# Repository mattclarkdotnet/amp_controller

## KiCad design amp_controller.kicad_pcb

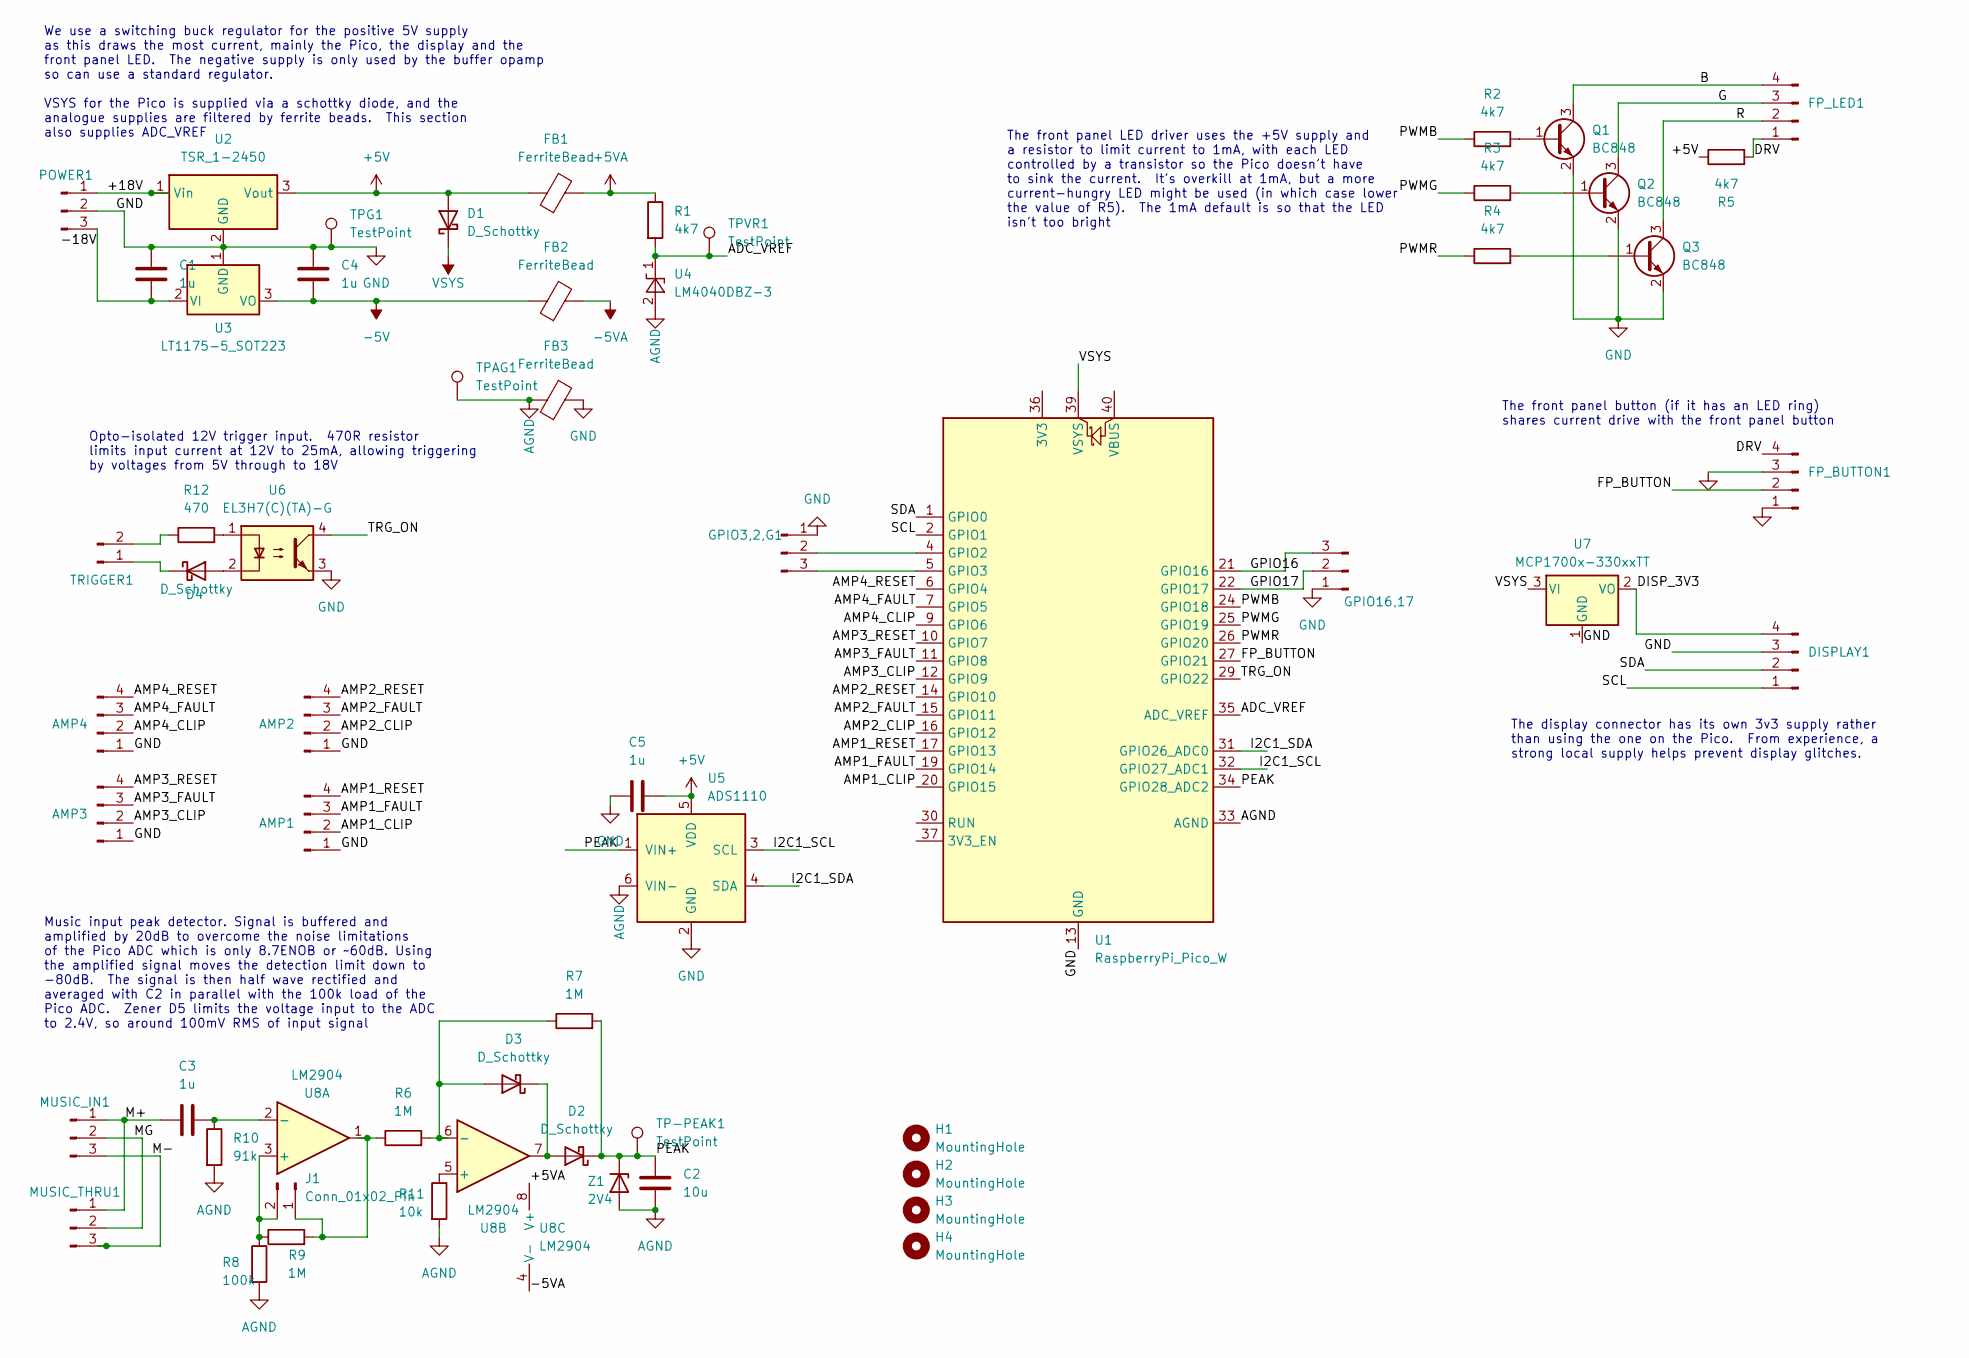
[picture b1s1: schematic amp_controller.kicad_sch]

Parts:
AMP1, AMP2, AMP3, AMP4: Conn_01x04_Pin; JST_EH_B4B-EH-A_1x04_P2.50mm_Vertical
C1, C3, C4, C5: 1u; C_0805_2012Metric; LCSC C28323
C2: 10u; C_0805_2012Metric; LCSC C440198
D1, D2, D3, D4: D_Schottky; D_SOD-523; LCSC C145179
DISPLAY1: Conn_01x04_Pin; JST_EH_B4B-EH-A_1x04_P2.50mm_Vertical
FB1, FB2, FB3: FerriteBead; L_0805_2012Metric; LCSC C1015
FP_BUTTON1: Conn_01x04_Pin; JST_EH_B4B-EH-A_1x04_P2.50mm_Vertical
FP_LED1: Conn_01x04_Pin; JST_EH_B4B-EH-A_1x04_P2.50mm_Vertical
GPIO3,2,G1, GPIO16,17: Conn_01x02_Pin; PinHeader_1x03_P2.54mm_Vertical
H1, H2, H3, H4: MountingHole; MountingHole_3.2mm_M3
J1: Conn_01x02_Pin; PinHeader_1x02_P2.54mm_Vertical
MUSIC_IN1: Conn_01x03_Pin; JST_EH_B3B-EH-A_1x03_P2.50mm_Vertical
MUSIC_THRU1: Conn_01x03_Pin; JST_EH_B3B-EH-A_1x03_P2.50mm_Vertical
POWER1: Conn_01x03_Pin; TerminalBlock_Phoenix_PT-1,5-3-3.5-H_1x03_P3.50mm_Horizontal
Q1, Q2, Q3: BC848; SOT-723; LCSC C2923360
R1, R2, R3, R4, R5: 4k7; R_0805_2012Metric; LCSC C17673
R6, R7, R9: 1M; R_0805_2012Metric; LCSC C17514
R8: 100k; R_0805_2012Metric; LCSC C149504
R10: 91k; R_0805_2012Metric; LCSC C2930321
R11: 10k; R_0805_2012Metric; LCSC C17414
R12: 470; R_0805_2012Metric; LCSC C17710
TP-PEAK1: TestPoint; TestPoint_THTPad_1.0x1.0mm_Drill0.5mm
TPAG1: TestPoint; TestPoint_THTPad_1.0x1.0mm_Drill0.5mm
TPG1: TestPoint; TestPoint_THTPad_1.0x1.0mm_Drill0.5mm
TPVR1: TestPoint; TestPoint_THTPad_1.0x1.0mm_Drill0.5mm
TRIGGER1: Conn_01x02_Pin; JST_EH_B2B-EH-A_1x02_P2.50mm_Vertical
U1: RaspberryPi_Pico_W; RaspberryPi_Pico_W_SMD
U2: TSR_1-2450; Converter_DCDC_TRACO_TSR-1_THT
U3: LT1175-5_SOT223; SOT-89-3; LCSC C122849
U4: LM4040DBZ-3; SOT-23; LCSC C181416
U5: ADS1110; SOT-23-6; LCSC C16598
U6: EL3H7(C)(TA)-G; SOIC-4_4.55x2.6mm_P1.27mm; LCSC C92243
U7: MCP1700x-330xxTT; SOT-23; LCSC C5446
U8: LM2904; SO-8_3.9x4.9mm_P1.27mm; LCSC C2941725
Z1: 2V4; D_SOD-323; LCSC C268469

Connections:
+5V: C5.2, D1.2 (A), FB1.1, R5.1, U2.3 (Vout), U5.5 (VDD)
+5VA: FB1.2, R1.1, U8.8 (V+)
-5V: C4.2, FB2.1, U3.3 (VO)
-5VA: FB2.2, U8.4 (V-)
/+18V: POWER1.1, U2.1 (Vin)
/-18V: C1.2, POWER1.3, U3.2 (VI)
/ADC_VREF: R1.2, TPVR1.1, U1.35 (ADC_VREF), U4.1 (K)
/AMP1_CLIP: AMP1.2, U1.20 (GPIO15)
/AMP1_FAULT: AMP1.3, U1.19 (GPIO14)
/AMP1_RESET: AMP1.4, U1.17 (GPIO13)
/AMP2_CLIP: AMP2.2, U1.16 (GPIO12)
/AMP2_FAULT: AMP2.3, U1.15 (GPIO11)
/AMP2_RESET: AMP2.4, U1.14 (GPIO10)
/AMP3_CLIP: AMP3.2, U1.12 (GPIO9)
/AMP3_FAULT: AMP3.3, U1.11 (GPIO8)
/AMP3_RESET: AMP3.4, U1.10 (GPIO7)
/AMP4_CLIP: AMP4.2, U1.9 (GPIO6)
/AMP4_FAULT: AMP4.3, U1.7 (GPIO5)
/AMP4_RESET: AMP4.4, U1.6 (GPIO4)
/B: FP_LED1.4, Q1.3 (C)
/DISP_3V3: DISPLAY1.4, U7.2 (VO)
/DRV: FP_BUTTON1.4, FP_LED1.1, R5.2
/FP_BUTTON: FP_BUTTON1.2, U1.27 (GPIO21)
/G: FP_LED1.3, Q2.3 (C)
/GPIO16: GPIO16,17.3, U1.21 (GPIO16)
/GPIO17: GPIO16,17.2, U1.22 (GPIO17)
/I2C1_SCL: U1.32 (GPIO27_ADC1), U5.3 (SCL)
/I2C1_SDA: U1.31 (GPIO26_ADC0), U5.4 (SDA)
/M+: C3.1, MUSIC_IN1.1, MUSIC_THRU1.1
/M-: MUSIC_IN1.3, MUSIC_THRU1.3
/MG: MUSIC_IN1.2, MUSIC_THRU1.2
/PEAK: C2.1, D2.1 (K), R7.2, TP-PEAK1.1, U1.34 (GPIO28_ADC2), U5.1 (VIN+), Z1.1 (K)
/PWMB: R2.1, U1.24 (GPIO18)
/PWMG: R3.1, U1.25 (GPIO19)
/PWMR: R4.1, U1.26 (GPIO20)
/R: FP_LED1.2, Q3.3 (C)
/SCL: DISPLAY1.1, U1.2 (GPIO1)
/SDA: DISPLAY1.2, U1.1 (GPIO0)
/TRG_ON: U1.29 (GPIO22), U6.4
AGND: C2.2, FB3.1, R8.2, R10.2, R11.2, TPAG1.1, U1.33 (AGND), U4.2 (A), U5.6 (VIN-), Z1.2 (A)
GND: AMP1.1, AMP2.1, AMP3.1, AMP4.1, C1.1, C4.1, C5.1, DISPLAY1.3, FB3.2, FP_BUTTON1.1, FP_BUTTON1.3, GPIO3,2,G1.1, GPIO16,17.1, POWER1.2, Q1.2 (E), Q2.2 (E), Q3.2 (E), TPG1.1, U1.3 (GND), U1.8 (GND), U1.13 (GND), U1.18 (GND), U1.23 (GND), U1.28 (GND), U1.38 (GND), U2.2 (GND), U3.1 (GND), U5.2 (GND), U6.3, U7.1 (GND)
unnamed: D2.2 (A), D3.1 (K), U8.7
unnamed: D3.2 (A), R6.2, R7.1, U8.6 (-)
unnamed: D4.2 (A), U6.2
unnamed: D4.1 (K), TRIGGER1.1
unnamed: GPIO3,2,G1.2, U1.4 (GPIO2)
unnamed: GPIO3,2,G1.3, U1.5 (GPIO3)
unnamed: J1.1, R6.1, R9.2, U8.1
unnamed: J1.2, R8.1, R9.1, U8.3 (+)
unnamed: Q1.1 (B), R2.2
unnamed: Q2.1 (B), R3.2
unnamed: Q3.1 (B), R4.2
unnamed: R12.2, U6.1
unnamed: R12.1, TRIGGER1.2
unnamed: C3.2, R10.1, U8.2 (-)
unnamed: R11.1, U8.5 (+)
VSYS: D1.1 (K), U1.39 (VSYS), U7.3 (VI)

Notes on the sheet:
Music input peak detector. Signal is buffered and amplified by 20dB to overcome the noise limitations of the Pico ADC which is only 8.7ENOB or ~60dB. Using the amplified signal moves the detection limit down to -80dB. The signal is then half wave rectified and averaged with C2 in parallel with the 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
The front panel button (if it has an LED ring) shares current drive with the front panel button
Opto-isolated 12V trigger input. 470R resistor limits input current at 12V to 25mA, allowing triggering by voltages from 5V through to 18V
The front panel LED driver uses the +5V supply and a resistor to limit current to 1mA, with each LED controlled by a transistor so the Pico doesn't have to sink the current. It's overkill at 1mA, but a more current-hungry LED might be used (in which case lower the value of R5). The 1mA default is s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
We use a switching buck regulator for the positive 5V supply as this draws the most current, mainly the Pico, the display and the front panel LED. The negative supply is only used by the buffer opamp so can use a standard regulator. VSYS for the Pico is supplied via a schottky diode, and the analog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
The display connector has its own 3v3 supply rather than using the one on the Pico. From experience, a strong local supply helps prevent display glitches.

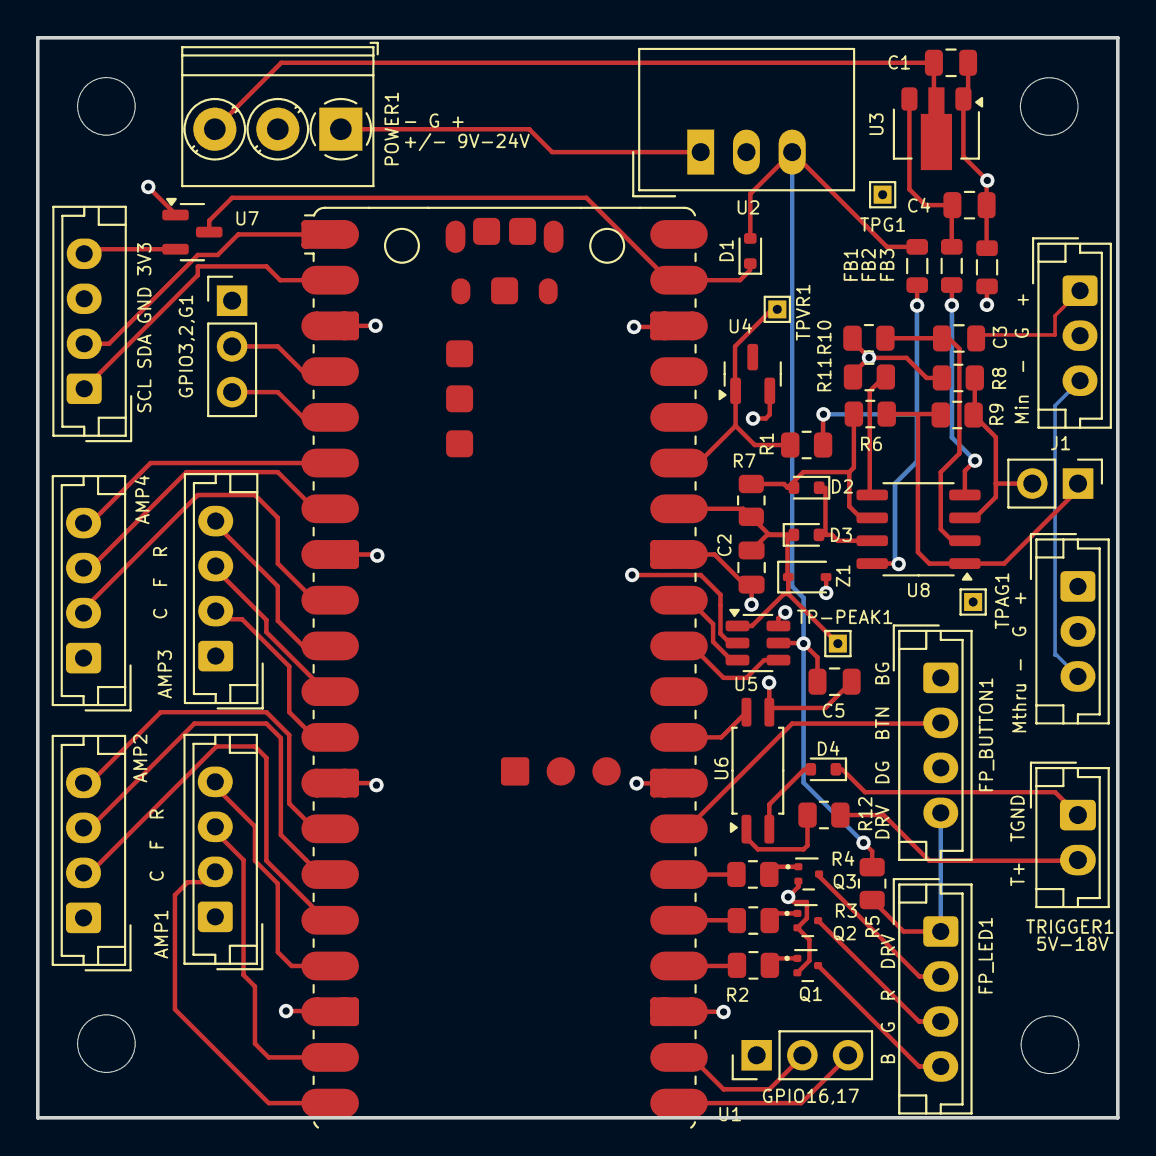
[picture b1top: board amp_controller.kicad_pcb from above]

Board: 4 copper layers, 60.0 x 60.0 mm, 58 parts (0 on the bottom side), 57 nets.

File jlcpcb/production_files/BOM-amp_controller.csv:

Comment,Designator,Footprint,LCSC
FerriteBead,"FB1,FB2,FB3",L_0805_2012Metric,C1015
LT1175-5_SOT223,U3,SOT-89-3,C122849
D_Schottky,"D1,D2,D3,D4",D_SOD-523,C145179
100k,R8,R_0805_2012Metric,C149504
ADS1110,U5,SOT-23-6,C16598
10k,R11,R_0805_2012Metric,C17414
1M,"R6,R7,R9",R_0805_2012Metric,C17514
4k7,"R1,R2,R3,R4,R5",R_0805_2012Metric,C17673
470,R12,R_0805_2012Metric,C17710
LM4040DBZ-3,U4,SOT-23,C181416
2V4,Z1,D_SOD-323,C268469
1u,"C1,C3,C4,C5",C_0805_2012Metric,C28323
BC848,"Q1,Q2,Q3",SOT-723,C2923360
91k,R10,R_0805_2012Metric,C2930321
LM2904,U8,SO-8_3.9x4.9mm_P1.27mm,C2941725
10u,C2,C_0805_2012Metric,C440198
MCP1700x-330xxTT,U7,SOT-23,C5446
EL3H7(C)(TA)-G,U6,SOIC-4_4.55x2.6mm_P1.27mm,C92243
Conn_01x02_Pin,"GPIO16,17",PinHeader_1x03_P2.54mm_Vertical,
Conn_01x02_Pin,"GPIO3,2,G1",PinHeader_1x03_P2.54mm_Vertical,
Conn_01x02_Pin,J1,PinHeader_1x02_P2.54mm_Vertical,

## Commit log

2024-05-04 passing DRC check, op amp input issue fixed
2024-06-08 tweaked layout and music sense resistors
